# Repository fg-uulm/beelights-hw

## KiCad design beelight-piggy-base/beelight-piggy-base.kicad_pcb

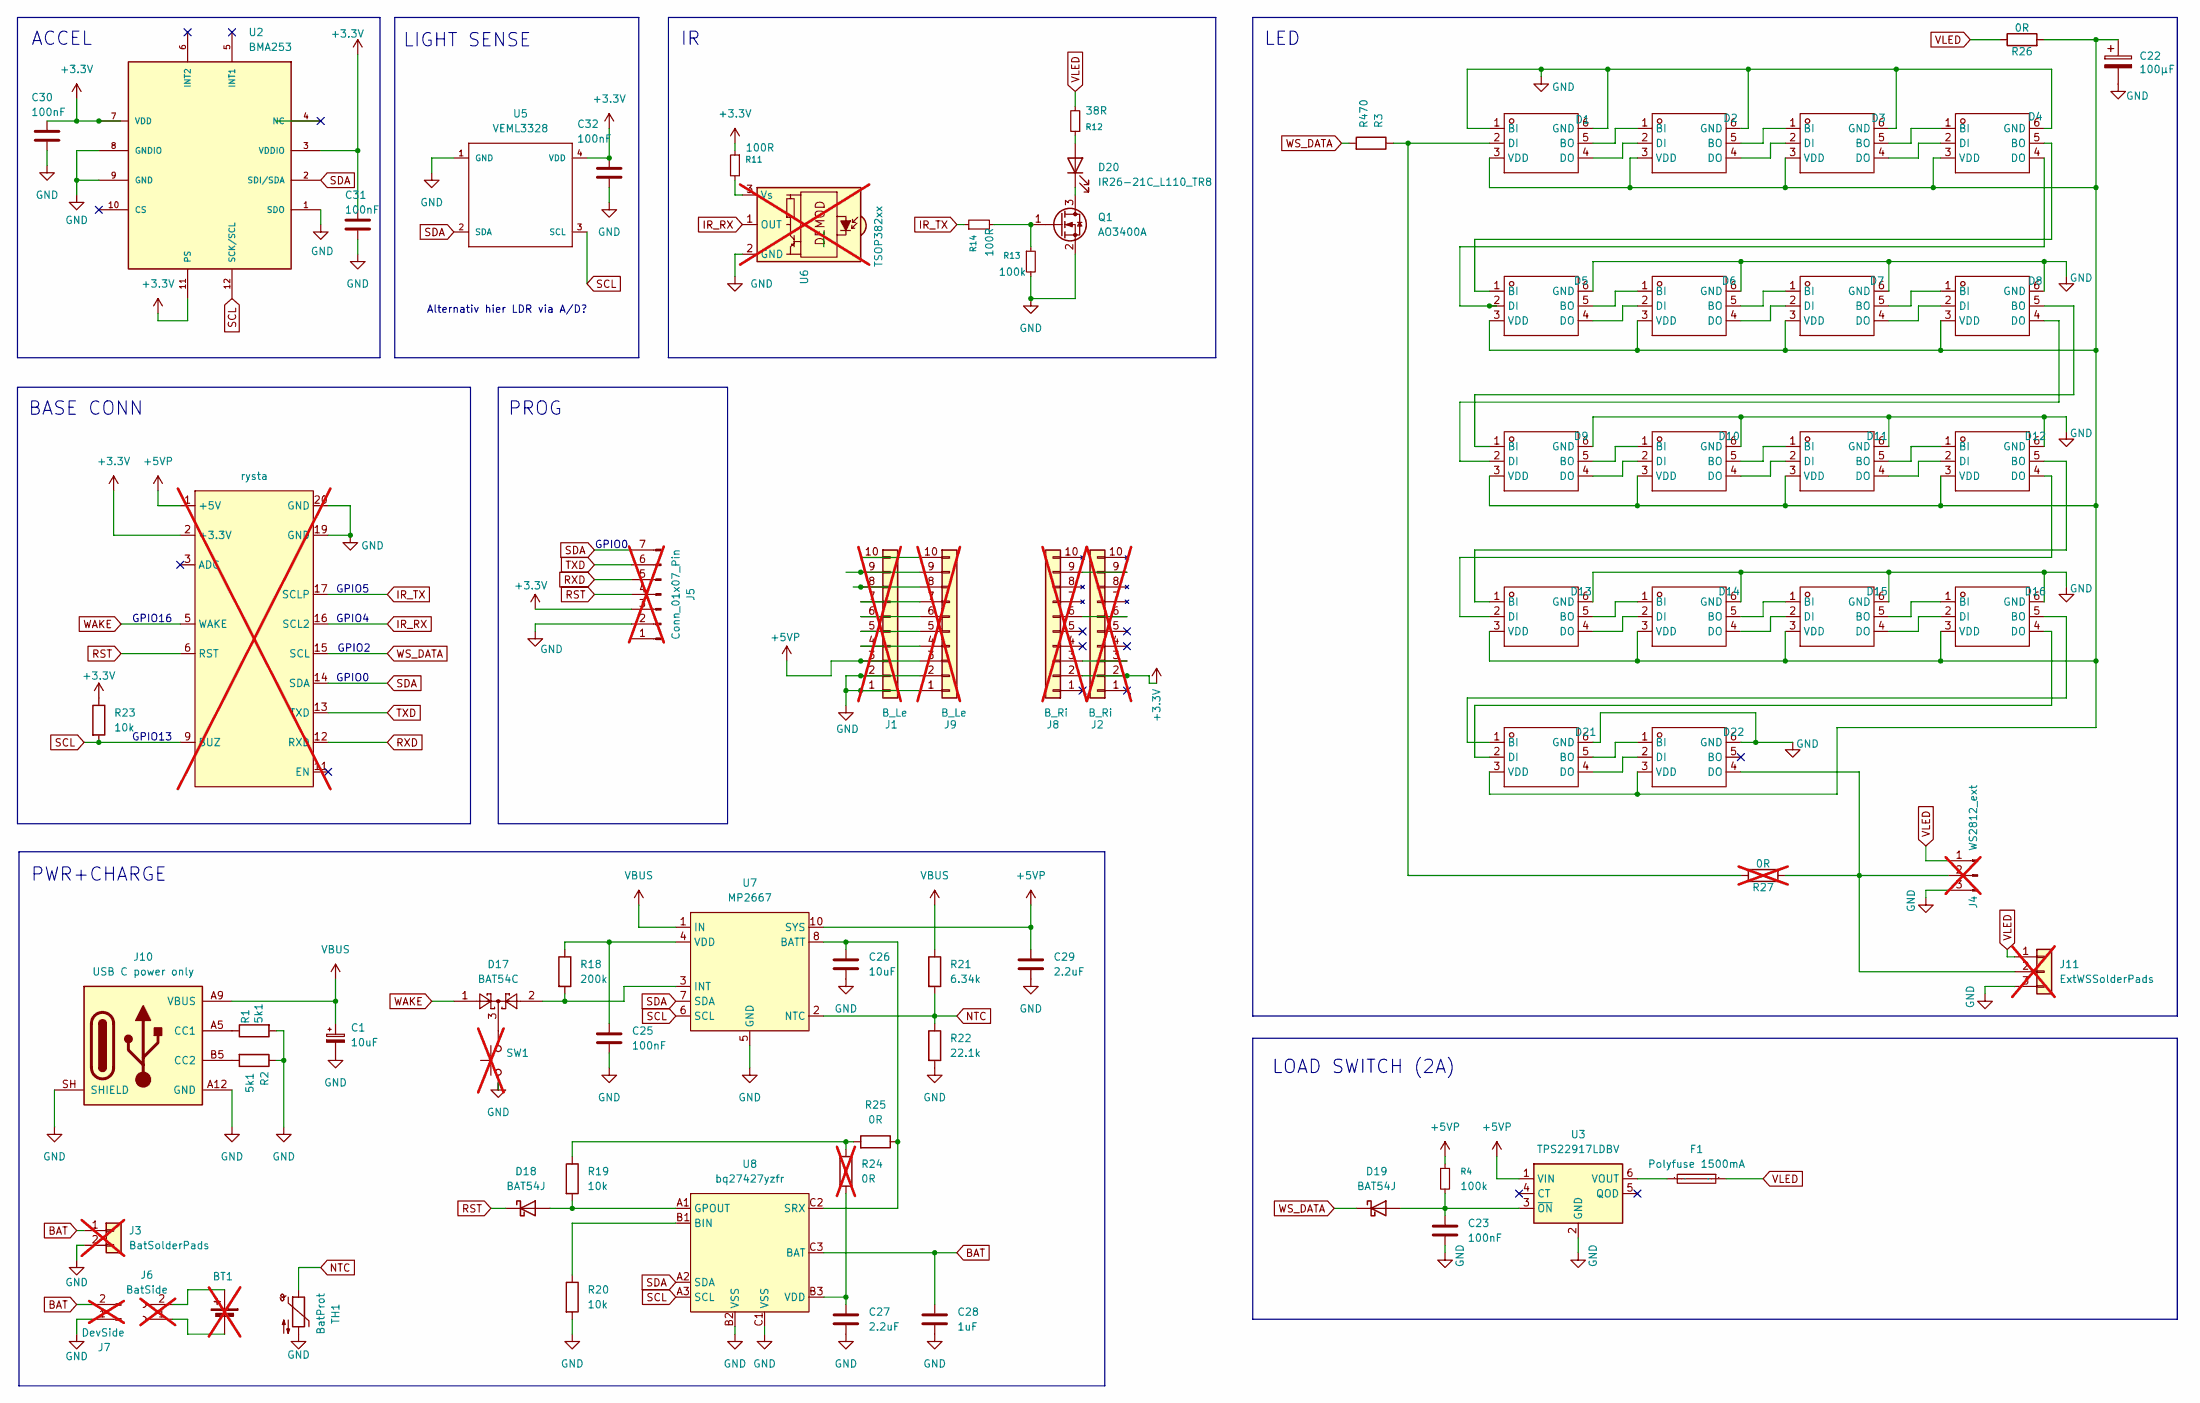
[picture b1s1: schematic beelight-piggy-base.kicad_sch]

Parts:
BT1: Battery_Cell; not fitted
C1: 10uF; C_1210_3225Metric
C22: 100µF; C_1210_3225Metric
C23, C25, C30, C31, C32: 100nF; C_0402_1005Metric
C26: 10uF; C_0805_2012Metric
C27: 2.2uF; C_0402_1005Metric
C28: 1uF; C_0603_1608Metric
C29: 2.2uF; C_0603_1608Metric
D1, D2, D3, D4, D5, D6, D7, D8, D9, D10, D11, D12, D13, D14, D15, D16, D21, D22: WS2812B; LED-SMD_6P-L2.2-W2.0_WS2816B-2020; Manufacturer Part WS2816B-2020; LCSC Part Name SMD灯珠
D17: BAT54C; SOT-23
D18, D19: BAT54J; D_SOD-323F
D20: IR26-21C_L110_TR8; LED_1206_3216Metric
F1: Polyfuse 1500mA; F0805; Manufacturer Part BSMD0805-050-12V; LCSC Part Name 12V 0.5A 0805自恢复
J1, J9: B_Le; PinHeader_1x10_P2.54mm_Vertical; not fitted
J2, J8: B_Ri; PinHeader_1x10_P2.54mm_Vertical; not fitted
J3: BatSolderPads; D_2114_3652Metric_Pad1.85x3.75mm_HandSolder; not fitted
J4: WS2812_ext; JST_GH_SM03B-GHS-TB_1x03-1MP_P1.25mm_Horizontal; not fitted
J5: Conn_01x07_Pin; PinSocket_1x07_P2.54mm_Vertical; not fitted
J6: BatSide; not fitted
J7: DevSide; JST_GH_SM02B-GHS-TB_1x02-1MP_P1.25mm_Horizontal; not fitted
J10: USB C power only; USB_C_Receptacle_GCT_USB4125-xx-x_6P_TopMnt_Horizontal
J11: ExtWSSolderPads; Resonator_SMD-3Pin_7.2x3.0mm_HandSoldering; not fitted
Q1: AO3400A; SOT-23
R1, R2: 5k1; R_0402_1005Metric
R3: R470; R_0402_1005Metric
R4, R13: 100k; R_0402_1005Metric
R11, R14: 100R; R_0402_1005Metric
R12: 38R; R_0402_1005Metric
R18: 200k; R_0402_1005Metric
R19, R20, R23: 10k; R_0402_1005Metric
R21: 6.34k; R_0402_1005Metric
R22: 22.1k; R_0402_1005Metric
R24, R27: 0R; R_1206_3216Metric; not fitted
R25, R26: 0R; R_1206_3216Metric
SW1: SW_Push; SW_Push_SPST_NO_Alps_SKRK; not fitted
TH1: BatProt; R_0805_2012Metric
U2: BMA253; LGA-12
U3: TPS22917LDBV; SOT-23-6
U4: rysta; not fitted
U5: VEML3328
U6: TSOP382xx; Vishay_MINICAST-3Pin; not fitted
U7: MP2667; QFN-10_2x2mm_P0.5mm
U8: bq27427yzfr; BGA-9_1.6x1.6mm_Layout3x3_P0.5mm

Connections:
+3.3V: C30.1, C31.1, C32.1, J2.2 (+3V3), J5.3, J8.2 (+3V3), R11.1, R23.1, U2.3 (VDDIO), U2.7 (VDD), U2.11 (PS), U4.2 (+3.3V), U5.4 (VDD)
+5VP: C29.1, J1.3 (REG), J9.3 (REG), R4.1, U3.1 (VIN), U4.1 (+5V), U7.10 (SYS)
BAT: C28.1, J3.1, J7.2, U8.C3 (BAT)
GND: C1.2, C22.2, C23.2, C25.2, C26.2, C27.2, C28.2, C29.2, C30.2, C31.2, C32.2, D1.1 (BI), D1.6 (GND), D2.6 (GND), D3.6 (GND), D4.6 (GND), D5.6 (GND), D6.6 (GND), D7.6 (GND), D8.6 (GND), D9.6 (GND), D10.6 (GND), D11.6 (GND), D12.6 (GND), D13.6 (GND), D14.6 (GND), D15.6 (GND), D16.6 (GND), D21.6 (GND), D22.6 (GND), J1.1 (GND), J1.2 (GND), J3.2, J4.3, J5.2, J7.1, J9.1 (GND), J9.2 (GND), J10.A12 (GND), J10.B12 (GND), J10.SH (SHIELD), J11.3, Q1.2 (S), R1.2, R2.1, R13.2, R20.2, R22.2, SW1.1, TH1.2, U2.1 (SDO), U2.8 (GNDIO), U2.9 (GND), U3.2 (GND), U4.19 (GND), U4.20 (GND), U5.1 (GND), U6.2 (GND), U7.5 (GND), U8.B2 (VSS), U8.C1 (VSS)
IR_RX: U4.16 (SCL2), U6.1 (OUT)
IR_TX: R14.1, U4.17 (SCLP)
NTC: R21.2, R22.1, TH1.1, U7.2 (NTC)
unnamed: BT1.1 (+), J6.2
unnamed: BT1.2 (-), J6.1
unnamed: D1.5 (BO), D2.1 (BI)
unnamed: D1.2 (DI), R3.1, R27.1
unnamed: D1.4 (DO), D2.2 (DI)
unnamed: C22.1, D1.3 (VDD), D2.3 (VDD), D3.3 (VDD), D4.3 (VDD), D5.3 (VDD), D6.3 (VDD), D7.3 (VDD), D8.3 (VDD), D9.3 (VDD), D10.3 (VDD), D11.3 (VDD), D12.3 (VDD), D13.3 (VDD), D14.3 (VDD), D15.3 (VDD), D16.3 (VDD), D21.3 (VDD), D22.3 (VDD), R26.2
unnamed: D2.5 (BO), D3.1 (BI)
unnamed: D2.4 (DO), D3.2 (DI)
unnamed: D3.5 (BO), D4.1 (BI)
unnamed: D3.4 (DO), D4.2 (DI)
unnamed: D4.5 (BO), D5.1 (BI)
unnamed: D4.4 (DO), D5.2 (DI)
unnamed: D5.5 (BO), D6.1 (BI)
unnamed: D5.4 (DO), D6.2 (DI)
unnamed: D6.5 (BO), D7.1 (BI)
unnamed: D6.4 (DO), D7.2 (DI)
unnamed: D7.5 (BO), D8.1 (BI)
unnamed: D7.4 (DO), D8.2 (DI)
unnamed: D8.5 (BO), D9.1 (BI)
unnamed: D8.4 (DO), D9.2 (DI)
unnamed: D9.5 (BO), D10.1 (BI)
unnamed: D10.5 (BO), D11.1 (BI)
unnamed: D9.4 (DO), D10.2 (DI)
unnamed: D10.4 (DO), D11.2 (DI)
unnamed: D11.5 (BO), D12.1 (BI)
unnamed: D11.4 (DO), D12.2 (DI)
unnamed: D12.5 (BO), D13.1 (BI)
unnamed: D12.4 (DO), D13.2 (DI)
unnamed: D13.5 (BO), D14.1 (BI)
unnamed: D13.4 (DO), D14.2 (DI)
unnamed: D14.5 (BO), D15.1 (BI)
unnamed: D14.4 (DO), D15.2 (DI)
unnamed: D15.5 (BO), D16.1 (BI)
unnamed: D15.4 (DO), D16.2 (DI)
unnamed: D16.5 (BO), D21.1 (BI)
unnamed: D16.4 (DO), D21.2 (DI)
unnamed: D17.3, SW1.2
unnamed: D18.2 (A), R19.2, U8.A1 (GPOUT)
unnamed: C23.1, D19.2 (A), R4.2, U3.3 (~ON)
unnamed: D20.2 (A), R12.1
unnamed: D20.1 (K), Q1.3 (D)
unnamed: D21.5 (BO), D22.1 (BI)
unnamed: D21.4 (DO), D22.2 (DI)
unnamed: D22.4 (DO), J4.2, J11.2, R27.2
unnamed: J1.4 (SCLP), J9.4 (SCLP)
unnamed: J1.5 (SCL2), J9.5 (SCL2)
unnamed: J1.6 (SCL), J9.6 (SCL)
unnamed: J1.7 (SDA), J9.7 (SDA)
unnamed: J1.8 (TXD), J9.8 (TXD)
unnamed: J1.9 (RXD), J9.9 (RXD)
unnamed: J1.10 (EN), J9.10 (EN)
unnamed: J2.3 (ADC), J8.3 (ADC)
unnamed: J2.6 (RST), J8.6 (RST)
unnamed: J2.9 (BUZ), J8.9 (BUZ)
unnamed: J10.A5 (CC1), R1.1
unnamed: J10.B5 (CC2), R2.2
unnamed: Q1.1 (G), R13.1, R14.2
unnamed: R19.1, R24.2, R25.2
unnamed: F1.2, U3.6 (VOUT)
unnamed: R11.2, U6.3 (Vs)
unnamed: D17.2, R18.2, U7.3 (INT)
unnamed: C25.1, R18.1, U7.4 (VDD)
unnamed: R20.1, U8.B1 (BIN)
unnamed: C26.1, R25.1, U7.8 (BATT), U7.9 (BATT), U8.C2 (SRX)
unnamed: C27.1, R24.1, U8.B3 (VDD)
RST: D18.1 (K), J5.4, U4.6 (RST)
RXD: J5.5, U4.12 (RXD)
SCL: R23.2, U2.12 (SCK/SCL), U4.9 (BUZ), U5.3 (SCL), U7.6 (SCL), U8.A3 (SCL)
SDA: J5.7, U2.2 (SDI/SDA), U4.14 (SDA), U5.2 (SDA), U7.7 (SDA), U8.A2 (SDA)
TXD: J5.6, U4.13 (TXD)
VBUS: C1.1, J10.A9 (VBUS), J10.B9 (VBUS), R21.1, U7.1 (IN)
VLED: F1.1, J4.1, J11.1, R12.2, R26.1
WAKE: D17.1, U4.5 (WAKE)
WS_DATA: D19.1 (K), R3.2, U4.15 (SCL)

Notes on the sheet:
ACCEL
Alternativ hier LDR via A/D?
BASE CONN
PROG
GPIO4
GPIO13
GPIO0
LED
GPIO16
LOAD SWITCH (2A)
GPIO5
GPIO2
PWR+CHARGE
LIGHT SENSE

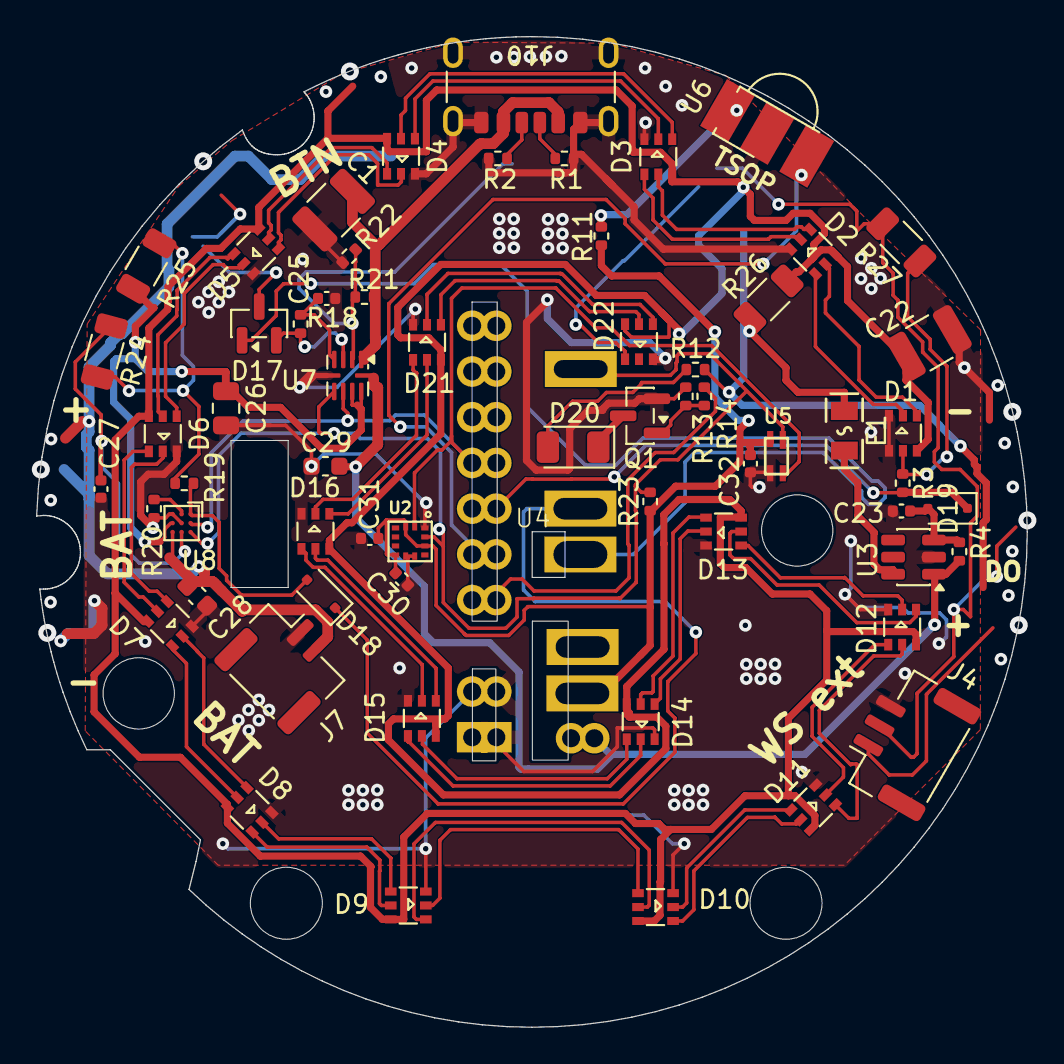
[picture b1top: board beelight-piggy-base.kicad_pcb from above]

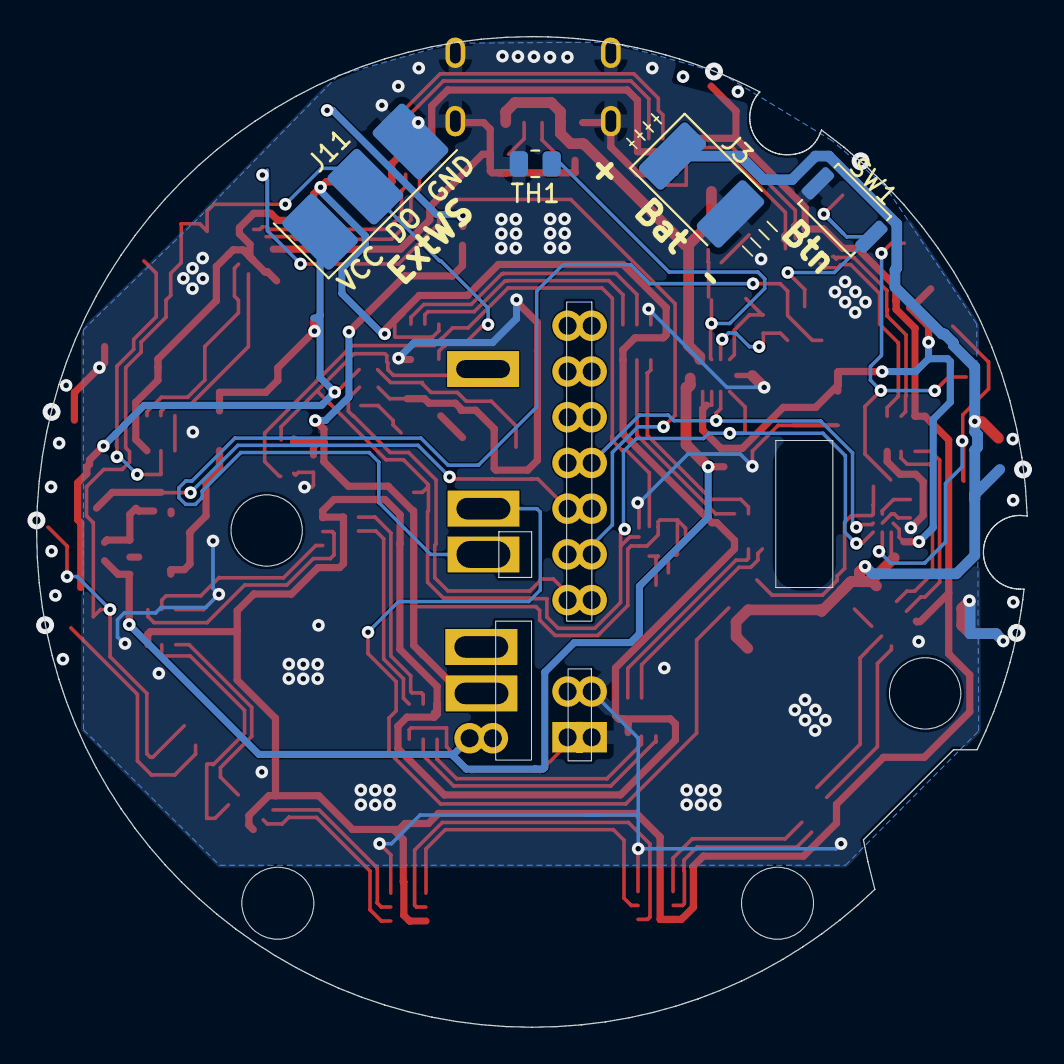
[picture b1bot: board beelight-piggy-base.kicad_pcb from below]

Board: 2 copper layers, 55.0 x 55.0 mm, 67 parts (4 on the bottom side), 67 nets.

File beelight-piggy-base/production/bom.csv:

Designator,Footprint,Quantity,Value,LCSC Part #
C1,1210,1,10µF,
C22,1210,1,100µF,
C23,0402,1,100n,
C25,0402,1,0.1uF,
C26,0805,1,10uF,
C27,0402,1,1uF,
C28,0603,1,1uF,
C29,0603,1,2.2uF,
"D1, D10, D11, D12, D13, D14, D15, D16, D2, D21, D22, D3, D4, D5, D6, D7, D8, D9",LED-SMD_6P-L2.2-W2.0_WS2816B-2020,18,WS2812B,
D17,SOT-23,1,BAT54C,
"D18, D19",D_SOD-323F,2,BAT54J,
D20,1206,1,IR26-21C_L110_TR8,
F1,1812,1,Polyfuse 1500mA,
J10,USB_C_Receptacle_GCT_USB4125-xx-x_6P_TopMnt_Horizontal,1,USB C power only,
J4,JST_GH_SM03B-GHS-TB_1x03-1MP_P1.25mm_Horizontal,1,WS2812_ext,
J7,JST_GH_SM02B-GHS-TB_1x02-1MP_P1.25mm_Horizontal,1,DevSide,
Q1,SOT-23,1,AO3400A,
"R1, R2",0402,2,5k1,
"R11, R14",0402,2,100R,
R12,0402,1,38R,
"R13, R4",0402,2,100k,
R18,0402,1,200k,
"R19, R20, R23",0402,3,10k,
"R21, R22",0402,2,100k tbd,
"R25, R26",0402,2,0R,
R3,0402,1,R470,
TH1,0805,1,BatProt,
U2,LGA-12,1,BMA253,
U3,SOT-23-6,1,TPS22917LDBV,
U4,rysta,1,rysta,
U5,VEML3328,1,VEML3328,
U7,QFN-10_2x2mm_P0.5mm,1,MP2667,
U8,BGA-9_1.6x1.6mm_Layout3x3_P0.5mm,1,BQ27421-G1,

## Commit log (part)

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2026-04-22 init
2026-05-11 first final proto
2026-05-13 alternative pwr, initial ver
2026-05-27 remove lock files for beelight-piggy-base
2026-05-27 add local symbol library and new footprints for BGA-9 and QFN-10
2026-05-27 add rysta footprint
2026-05-27 fix rysta symbol
2026-05-27 update .gitignore to include beelight-piggy-base backups
2026-05-27 add rysta symbol to schematic
2026-05-27 add Schottky diode symbol to library
2026-05-27 rewire existing components
2026-05-27 add replace power and charge section
2026-05-31 add push button switch symbol to library
2026-05-31 add pull-up for SCL, change gpout pull-up connection and add wake button
2026-05-31 use WS_DATA for load switch
2026-06-01 fix D23 orientation
2026-06-01 fix usb-c input cc resistors
2026-06-01 rewire gpout pull-up to vdd
2026-06-20 ws2816, schottky diodes added, used 0r for jprs
2026-06-21 pre jlc proto order
2026-06-21 last minor fixes pre order
2026-06-21 more minor minor fixes pre proto order
2026-06-22 tius feedback
2026-06-22 tius feedback 2
2026-06-22 tius feedback 2 - fix drc issues
2026-06-22 tius feedback 2 - copper cleanup
2026-06-22 PROTOTYPE ORDER - minor fixes + new board outline
